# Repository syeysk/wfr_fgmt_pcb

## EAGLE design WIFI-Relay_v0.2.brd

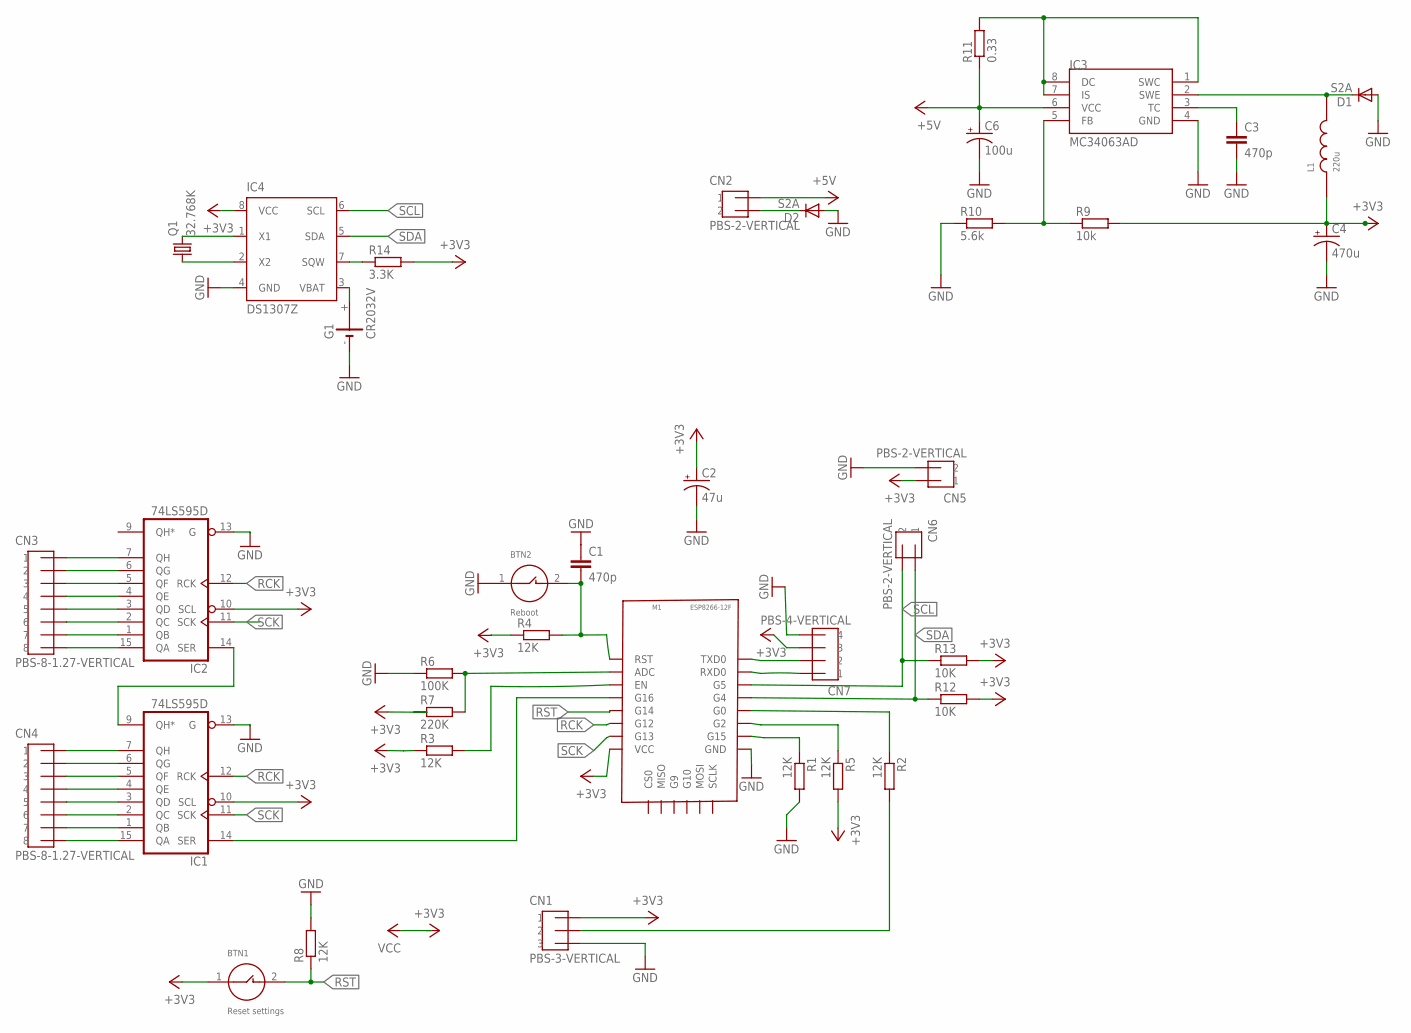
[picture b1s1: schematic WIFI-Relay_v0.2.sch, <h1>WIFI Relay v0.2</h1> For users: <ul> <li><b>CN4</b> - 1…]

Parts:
BTN1: Reset settings; BTN-6X4-SMD
BTN2: Reboot; BTN-6X4-SMD
C1, C3: 470p; C0603
C2: 47u; CT3216
C4: 470u; D/7343-31W
C6: 100u; D/7343-31W
CN1: PBS-3-VERTICAL
CN2, CN5, CN6: PBS-2-VERTICAL
CN3, CN4: PBS-8-1.27-VERTICAL
CN7: PBS-4-VERTICAL
D1, D2: S2A; DO214AA
G1: CR2032V
IC1, IC2: 74LS595D; SO16
IC3: MC34063AD; SOIC8
IC4: DS1307Z; SOIC8
L1: 220u; INDUCTOR-5-10
M1: ESP8266-12F
Q1: 32.768K; TC38H
R1, R2, R3, R4, R5, R8: 12K; R0603
R6: 100K; R0603
R7: 220K; R0603
R9: 10k; R0603
R10: 5.6k; R0603
R11: 0.33; R0603
R12, R13: 10K; R0603
R14: 3.3K; R0603

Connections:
+3V3: BTN1.1, C2.- (+), C4.+, CN1.P$1 (1), CN5.P$1 (1), CN7.P$3 (3), IC1.10 (SCL), IC1.16 (VCC), IC2.10 (SCL), IC2.16 (VCC), IC4.8 (VCC), L1.P$1 (1), M1.VCC, R3.1, R4.1, R5.2, R7.1, R9.2, R12.2, R13.2, R14.2
+5V: C6.+, CN2.P$1 (1), IC3.6 (VCC), R11.1
GND: BTN2.1, C1.1, C2.+ (-), C3.2, C4.-, C6.-, CN1.P$3 (3), CN5.P$2 (2), CN7.P$4 (4), D1.A, D2.A, G1.-, IC1.8 (GND), IC1.13 (G), IC2.8 (GND), IC2.13 (G), IC3.4 (GND), IC4.4 (GND), M1.GND, R1.2, R6.1, R8.2, R10.1
unnamed: M1.G15, R1.1
unnamed: M1.G2, R5.1
unnamed: M1.G0, R2.1
unnamed: CN1.P$2 (2), R2.2
unnamed: M1.EN, R3.2
unnamed: CN7.P$1 (1), M1.RXD0
unnamed: CN7.P$2 (2), M1.TXD0
unnamed: CN3.P$1 (1), IC2.7 (QH)
unnamed: CN3.P$2 (2), IC2.6 (QG)
unnamed: CN3.P$3 (3), IC2.5 (QF)
unnamed: CN3.P$4 (4), IC2.4 (QE)
unnamed: CN3.P$5 (5), IC2.3 (QD)
unnamed: CN3.P$6 (6), IC2.2 (QC)
unnamed: CN3.P$7 (7), IC2.1 (QB)
unnamed: CN3.P$8 (8), IC2.15 (QA)
unnamed: CN4.P$1 (1), IC1.7 (QH)
unnamed: CN4.P$2 (2), IC1.6 (QG)
unnamed: CN4.P$3 (3), IC1.5 (QF)
unnamed: CN4.P$4 (4), IC1.4 (QE)
unnamed: CN4.P$5 (5), IC1.3 (QD)
unnamed: CN4.P$6 (6), IC1.2 (QC)
unnamed: CN4.P$7 (7), IC1.1 (QB)
unnamed: CN4.P$8 (8), IC1.15 (QA)
unnamed: BTN2.2, C1.2, M1.RST, R4.2
unnamed: IC4.1 (X1), Q1.2
unnamed: IC1.9 (QH*), IC2.14 (SER)
unnamed: IC1.14 (SER), M1.G16
unnamed: IC4.2 (X2), Q1.1
unnamed: M1.ADC, R6.2, R7.2
unnamed: IC3.5 (FB), R9.1, R10.2
unnamed: D1.C, IC3.2 (SWE), L1.P$2
unnamed: IC3.1 (SWC), IC3.7 (IS), IC3.8 (DC), R11.2
unnamed: C3.1, IC3.3 (TC)
unnamed: CN2.P$2 (2), D2.C
unnamed: IC4.7 (SQW), R14.1
unnamed: G1.+, IC4.3 (VBAT)
RCK: IC1.12 (RCK), IC2.12 (RCK), M1.G12
RST: BTN1.2, M1.G14, R8.1
SCK: IC1.11 (SCK), IC2.11 (SCK), M1.G13
SCL: CN6.P$2 (2), IC4.6 (SCL), M1.G5, R13.1
SDA: CN6.P$1 (1), IC4.5 (SDA), M1.G4, R12.1

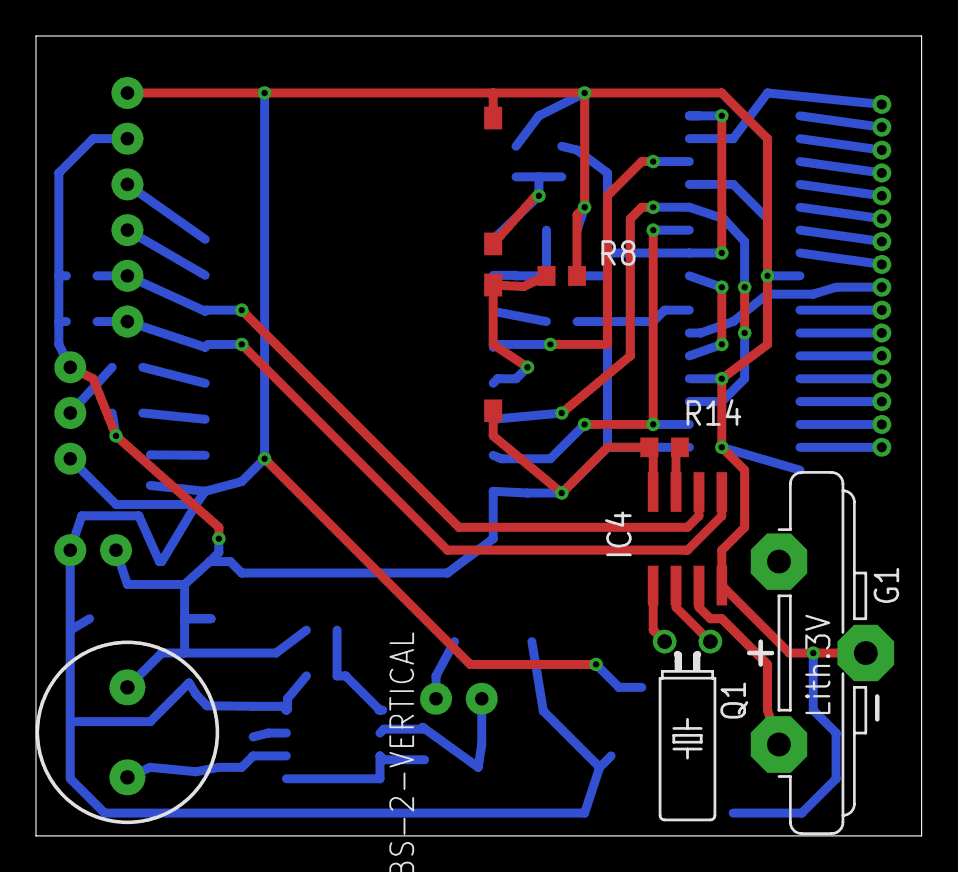
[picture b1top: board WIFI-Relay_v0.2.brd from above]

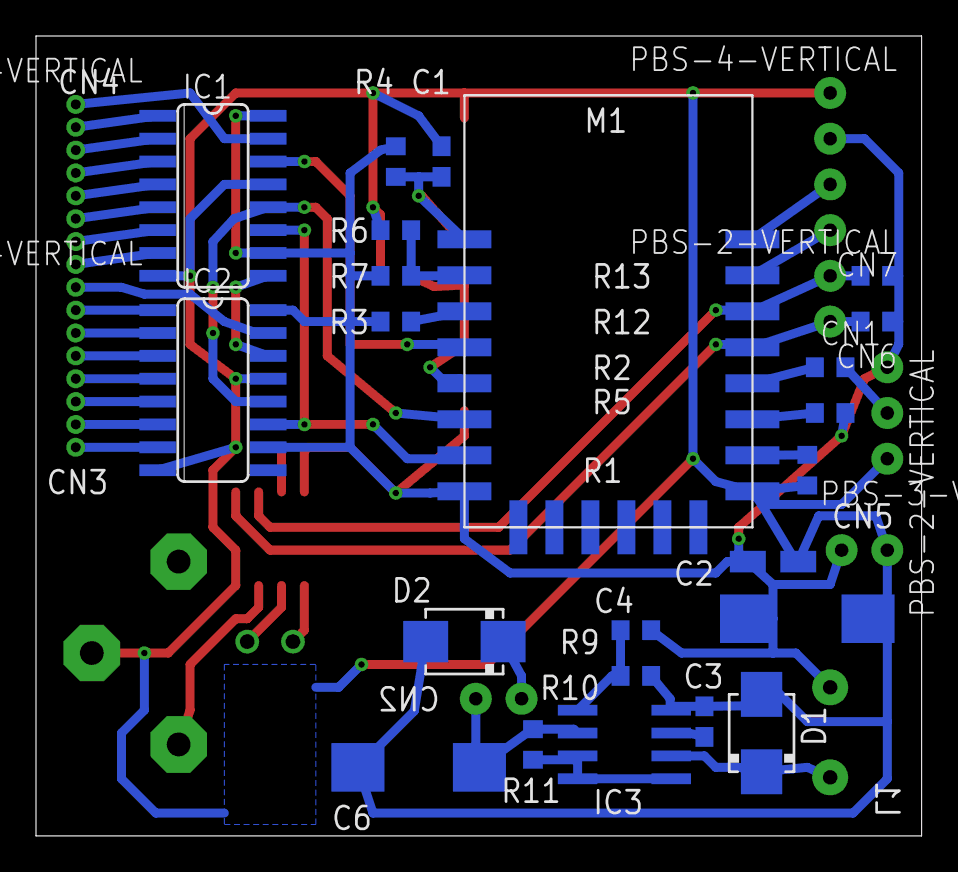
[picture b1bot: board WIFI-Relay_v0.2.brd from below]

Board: 2 copper layers, 49.2 x 44.4 mm, 38 parts (29 on the bottom side), 44 nets.

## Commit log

2018-05-12 first commmit
2018-05-13 LICENCE was added
2018-05-15 Button "Reset settings" was replaced with N$27
2018-05-16 Scheme of mc34036 was replaced into main sheet.
2018-09-20 submodule with eagle libs was added
2018-10-14 Value and name were changed. Eagle is 9.2.0
